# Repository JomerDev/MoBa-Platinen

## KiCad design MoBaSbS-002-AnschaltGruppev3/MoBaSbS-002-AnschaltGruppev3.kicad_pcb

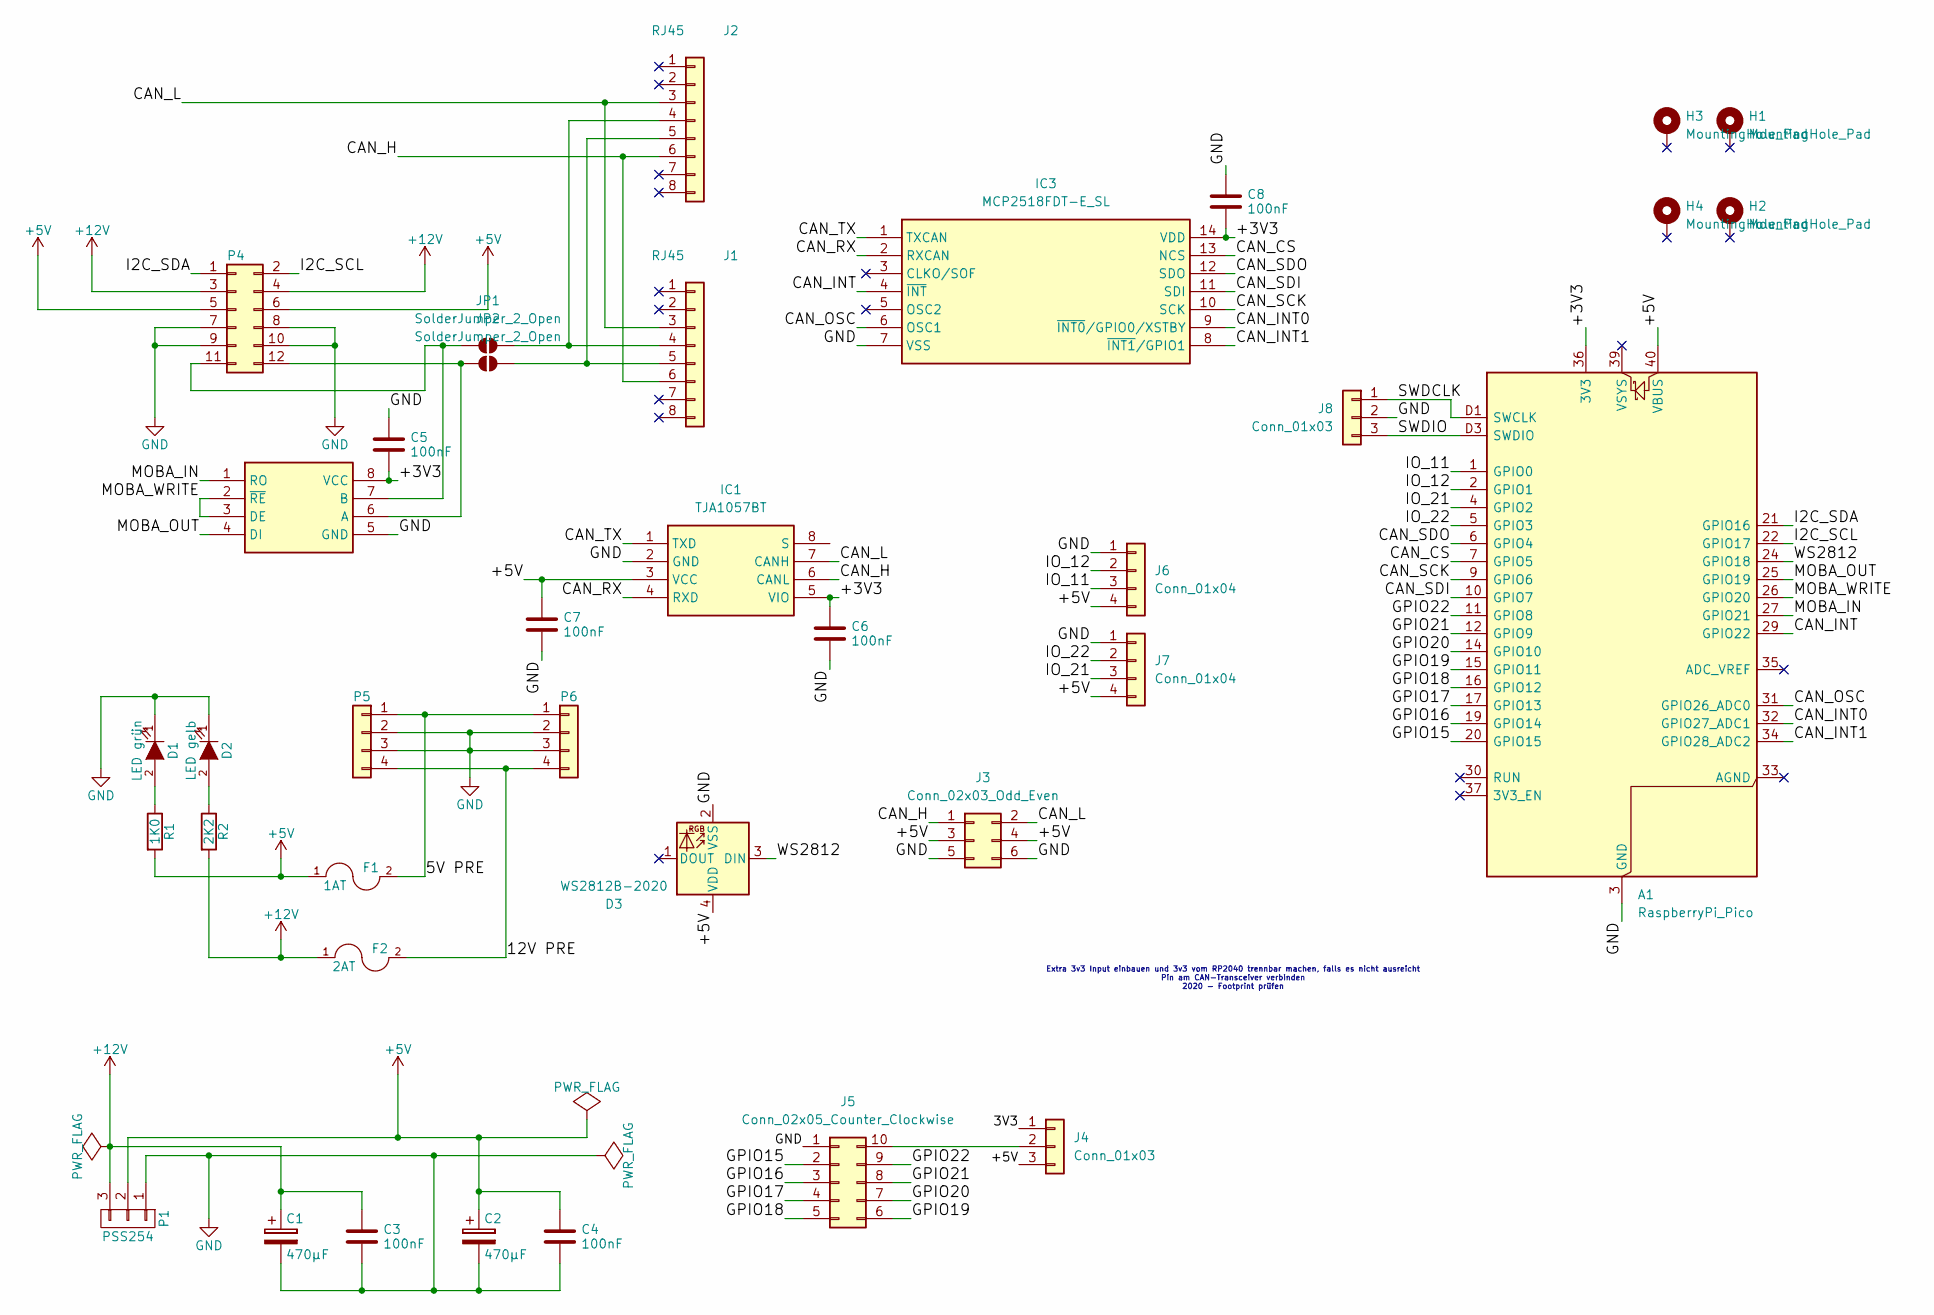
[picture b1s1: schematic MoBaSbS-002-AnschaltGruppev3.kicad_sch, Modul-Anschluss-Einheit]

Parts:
A1: RaspberryPi_Pico; RaspberryPi_Pico_Original_SMD_HandSolder
C1, C2: 470µF; CP_Radial_D8.0mm_P5.00mm
C3, C4: 100nF; C_1206_3216Metric
C5, C6, C7, C8: 100nF; C_0603_1608Metric
D1: LED grün; LED_1206_3216Metric
D2: LED gelb; LED_1206_3216Metric
D3: WS2812B-2020; LED_WS2812B-2020_PLCC4_2.0x2.0mm
F1: 1AT; Fuseholder_Littelfuse_Nano2_154x
F2: 2AT; Fuseholder_Littelfuse_Nano2_154x
H1, H2, H3, H4: MountingHole_Pad; MountingHole_2.7mm_M2.5_DIN965_Pad
IC1: TJA1057BT; SOIC127P600X175-8N; Manufacturer_Part_Number TJA1057BT
IC2: SP3485EN-L_TR; SOIC127P600X175-8N; Mouser Part Number 701-SP3485EN-L/TR
IC3: MCP2518FDT-E_SL; SOIC127P600X175-14N; Mouser Part Number 579-MCP2518FDT-E/SL
J1, J2: RJ45; RJ45_8
J3: Conn_02x03_Odd_Even; PinSocket_2x03_P2.54mm_Horizontal
J4, J8: Conn_01x03; PinHeader_1x03_P2.54mm_Vertical
J5: Conn_02x05_Counter_Clockwise; IDC-Header_2x05_P2.54mm_Vertical
J6, J7: Conn_01x04; Molex_KK-254_AE-6410-04A_1x04_P2.54mm_Vertical
JP1, JP2: SolderJumper_2_Open; SolderJumper-2_P1.3mm_Open_RoundedPad1.0x1.5mm
P1: PSS254; Molex_KK-254_AE-6410-03A_1x03_P2.54mm_Vertical
P4: 2x5_Buchse; PinSocket_2x06_P2.54mm_Horizontal
P5, P6: Wago; CONN_5566-04A_MOL
R1: 1K0; R_1206_3216Metric
R2: 2K2; R_1206_3216Metric

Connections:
+5V: A1.40 (VBUS), C2.1, C4.1, C7.1, D3.4 (VDD), F1.1, IC1.3 (VCC), J3.3, J3.4, J4.3, J6.4, J7.4, P1.2, P4.5, P4.6, R1.2
+12V: C1.1, C3.1, F2.1, P1.3, P4.3, P4.4, R2.2
/3V3: J4.1
/5V PRE: F1.2, P5.1, P6.1
/12V PRE: F2.2, P5.4, P6.4
/+3V3: A1.36 (3V3), C5.2, C6.1, C8.2, IC1.5 (VIO), IC2.8 (VCC), IC3.14 (VDD)
/CAN_CS: A1.7 (GPIO5), IC3.13 (NCS)
/CAN_H: IC1.6 (CANL), J1.6, J2.6, J3.1
/CAN_INT: A1.29 (GPIO22), IC3.4 (~INT)
/CAN_INT0: A1.32 (GPIO27_ADC1), IC3.9 (~INT0/GPIO0/XSTBY)
/CAN_INT1: A1.34 (GPIO28_ADC2), IC3.8 (~INT1/GPIO1)
/CAN_L: IC1.7 (CANH), J1.3, J2.3, J3.2
/CAN_OSC: A1.31 (GPIO26_ADC0), IC3.6 (OSC1)
/CAN_RX: IC1.4 (RXD), IC3.2 (RXCAN)
/CAN_SCK: A1.9 (GPIO6), IC3.10 (SCK)
/CAN_SDI: A1.10 (GPIO7), IC3.11 (SDI)
/CAN_SDO: A1.6 (GPIO4), IC3.12 (SDO)
/CAN_TX: IC1.1 (TXD), IC3.1 (TXCAN)
/GPIO15: A1.20 (GPIO15), J5.2
/GPIO16: A1.19 (GPIO14), J5.3
/GPIO17: A1.17 (GPIO13), J5.4
/GPIO18: A1.16 (GPIO12), J5.5
/GPIO19: A1.15 (GPIO11), J5.6
/GPIO20: A1.14 (GPIO10), J5.7
/GPIO21: A1.12 (GPIO9), J5.8
/GPIO22: A1.11 (GPIO8), J5.9
/I2C_SCL: A1.22 (GPIO17), P4.2
/I2C_SDA: A1.21 (GPIO16), P4.1
/IO_11: A1.1 (GPIO0), J6.3
/IO_12: A1.2 (GPIO1), J6.2
/IO_21: A1.4 (GPIO2), J7.3
/IO_22: A1.5 (GPIO3), J7.2
/MOBA_IN: A1.27 (GPIO21), IC2.1 (RO)
/MOBA_OUT: A1.25 (GPIO19), IC2.4 (DI)
/MOBA_WRITE: A1.26 (GPIO20), IC2.2 (~RE), IC2.3 (DE)
/SWDCLK: A1.D1 (SWCLK), J8.1
/SWDIO: A1.D3 (SWDIO), J8.3
/WS2812: A1.24 (GPIO18), D3.3 (DIN)
GND: A1.3 (GND), A1.8 (GND), A1.13 (GND), A1.18 (GND), A1.23 (GND), A1.28 (GND), A1.38 (GND), A1.D2 (GND), C1.2, C2.2, C3.2, C4.2, C5.1, C6.2, C7.2, C8.1, D1.1 (K), D2.1 (K), D3.2 (VSS), IC1.2 (GND), IC2.5 (GND), IC3.7 (VSS), J3.5, J3.6, J5.1, J6.1, J7.1, J8.2, P1.1, P4.7, P4.8, P4.9, P4.10, P5.2, P5.3, P6.2, P6.3
unnamed: D1.2 (A), R1.1
unnamed: D2.2 (A), R2.1
unnamed: IC2.6 (A), JP2.1 (A), P4.12
unnamed: IC2.7 (B), JP1.1 (A), P4.11
unnamed: J1.4, J2.4, JP1.2 (B)
unnamed: J1.5, J2.5, JP2.2 (B)
unnamed: J4.2, J5.10

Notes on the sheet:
Extra 3v3 Input einbauen und 3v3 vom RP2040 trennbar machen, falls es nicht ausreicht Pin am CAN-Transceiver verbinden 2020 - Footprint prüfen

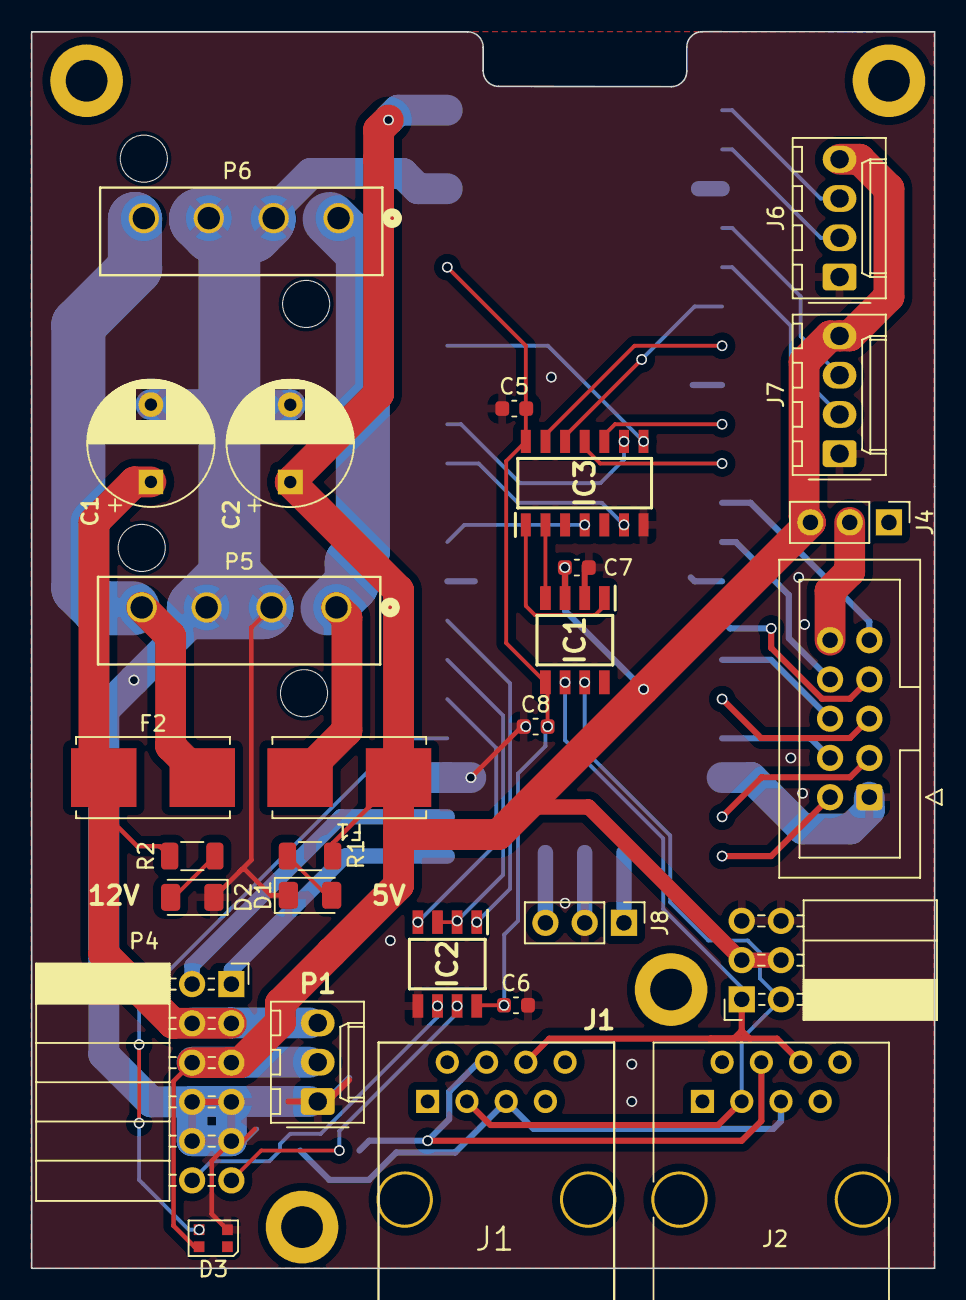
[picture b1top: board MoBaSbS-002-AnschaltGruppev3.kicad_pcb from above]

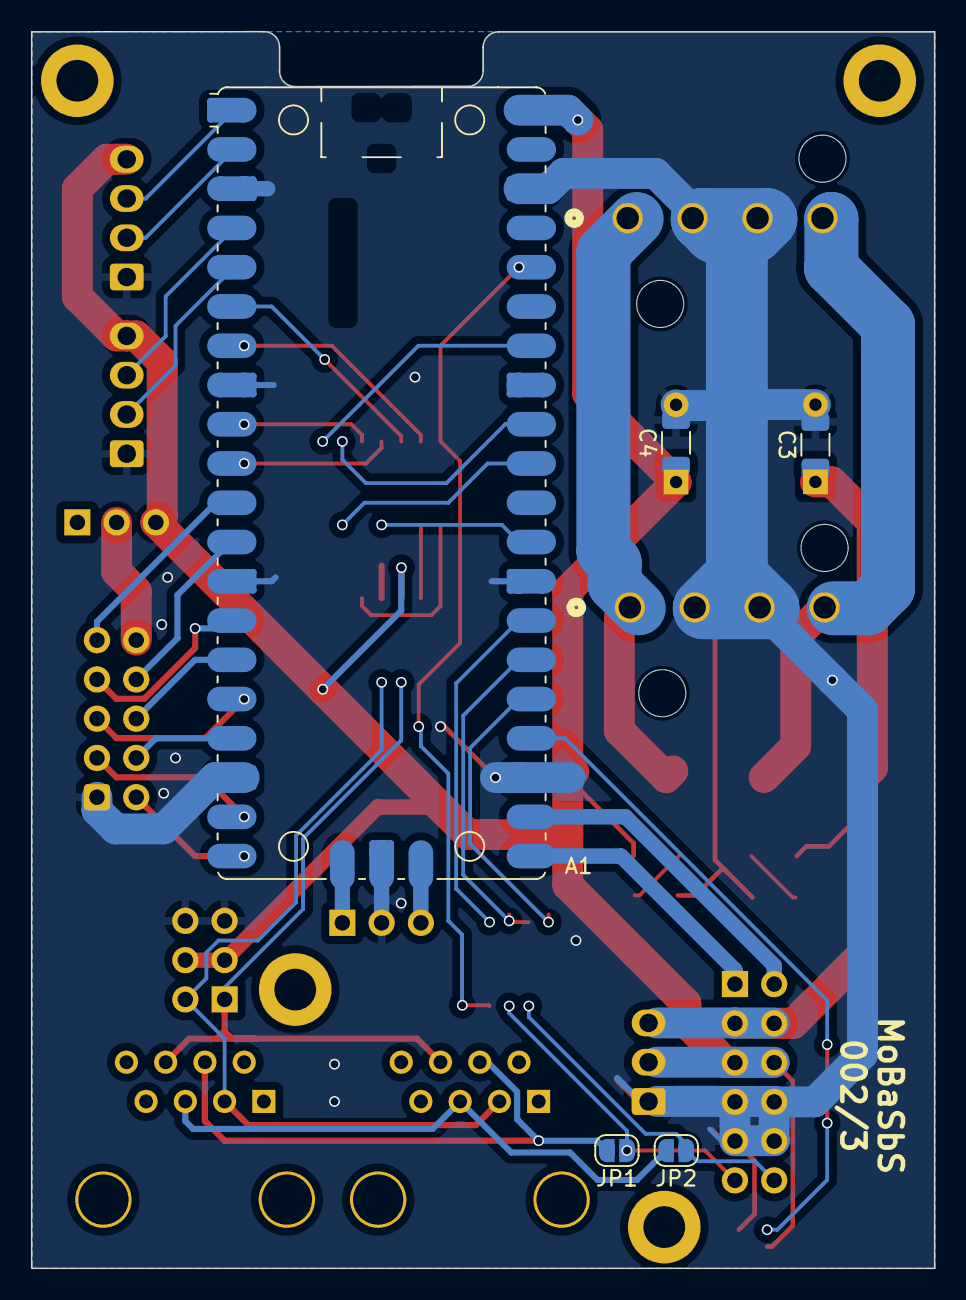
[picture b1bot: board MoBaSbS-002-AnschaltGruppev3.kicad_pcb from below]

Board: 2 copper layers, 58.4 x 80.0 mm, 37 parts (5 on the bottom side), 45 nets.

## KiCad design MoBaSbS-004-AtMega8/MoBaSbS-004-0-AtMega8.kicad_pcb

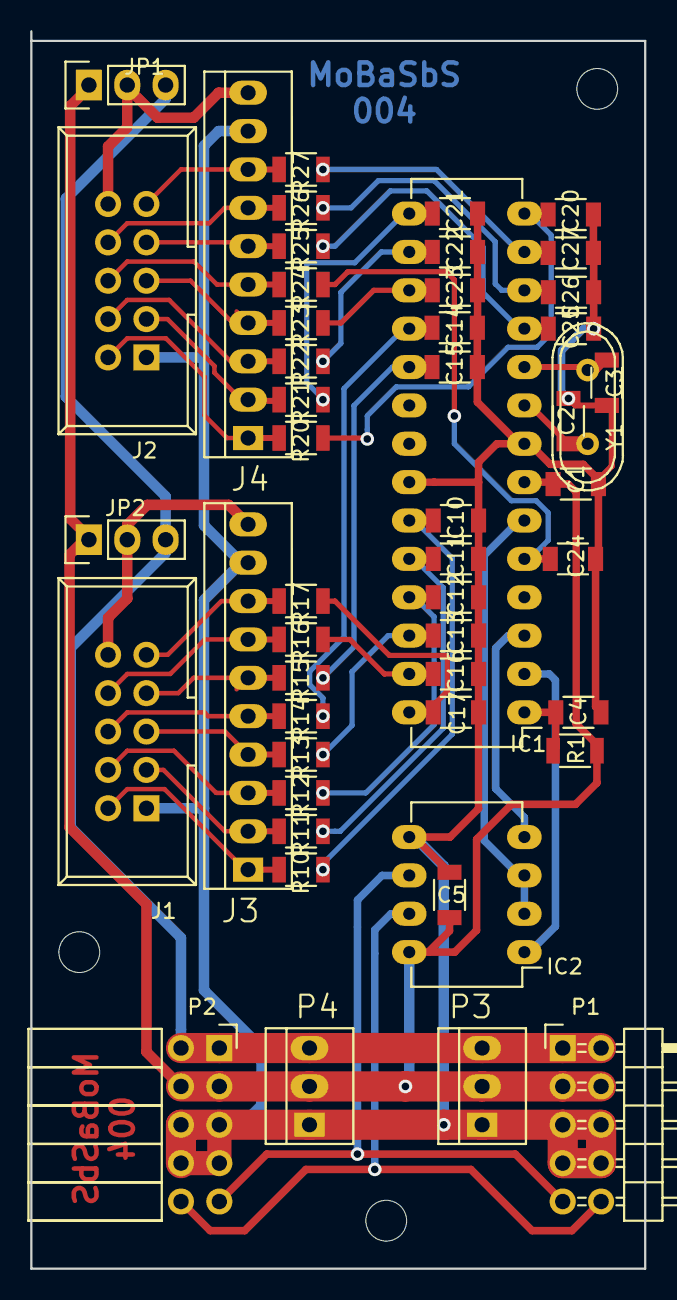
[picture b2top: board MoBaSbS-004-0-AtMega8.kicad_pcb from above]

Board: 2 copper layers, 40.6 x 81.9 mm, 51 parts (0 on the bottom side), 45 nets.

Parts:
C1, C4, C5: 100nF; C_1206
C2, C3: 33pF; C_1206
C10, C11, C12, C13, C14, C15, C16, C17, C20, C21, C22, C23, C24, C25, C26, C27: 47nF; C_1206
IC1: ATMEGA8A-P; DIP-28_W7.62mm_LongPads
IC2: MAX485; DIP-8_W7.62mm_LongPads
J1, J2: 10-Flachband; IDC_Header_Straight_10pins
J3, J4: PSS254-10P; PSS254-10G
JP1, JP2: JUMPER3; Pin_Header_Straight_1x03
P1: CONN_02X05; Pin_Header_Angled_2x05
P2: CONN_02X05; Socket_Strip_Angled_2x05
P3, P4: PSS-3G; PSS254-3G
R1: 10K0; R_1206
R10, R11, R12, R13, R14, R15, R16, R17, R20, R21, R22, R23, R24, R25, R26, R27: R; R_1206
Y1: 8MHz; Crystal_HC49-U_Vertical

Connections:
+5V: C1.1, C5.1, IC1.7, IC2.8, JP1.1, JP2.1, P1.3, P1.4, P2.3, P2.4, P3.2, P4.2, R1.1
+12V: JP1.3, JP2.3, P1.1, P1.2, P2.1, P2.2, P3.3, P4.3
GND: C1.2, C2.2, C3.2, C4.2, C5.2, C10.1, C11.1, C12.1, C13.1, C14.1, C15.1, C16.1, C17.1, C20.1, C21.1, C22.1, C23.1, C24.1, C25.1, C26.1, C27.1, IC1.8, IC1.22, IC2.5, J1.1, J2.1, J3.9, J4.9, P1.5, P1.6, P1.7, P1.8, P2.5, P2.6, P2.7, P2.8, P3.1, P4.1
unnamed: C2.1, IC1.9, Y1.1
unnamed: C3.1, IC1.10, Y1.2
unnamed: C4.1, IC1.1, R1.2
unnamed: C10.2, IC1.23, R10.2
unnamed: C11.2, IC1.24, R11.2
unnamed: C12.2, IC1.25, R12.2
unnamed: C13.2, IC1.26, R13.2
unnamed: C14.2, IC1.18, R14.2
unnamed: C15.2, IC1.19, R15.2
unnamed: C16.2, IC1.27, R16.2
unnamed: C17.2, IC1.28, R17.2
unnamed: C20.2, IC1.14, R20.2
unnamed: C21.2, IC1.15, R21.2
unnamed: C22.2, IC1.16, R22.2
unnamed: C23.2, IC1.17, R23.2
unnamed: C24.2, IC1.5, R24.2
unnamed: C25.2, IC1.11, R25.2
unnamed: C26.2, IC1.12, R26.2
unnamed: C27.2, IC1.13, R27.2
unnamed: IC1.2, IC2.1
unnamed: IC1.3, IC2.4
unnamed: IC1.6, IC2.2, IC2.3
unnamed: IC2.6, P1.9, P2.9
unnamed: IC2.7, P1.10, P2.10
unnamed: J1.2, J3.1, R10.1
unnamed: J1.3, J3.2, R11.1
unnamed: J1.4, J3.3, R12.1
unnamed: J1.5, J3.4, R13.1
unnamed: J1.6, J3.5, R14.1
unnamed: J1.7, J3.6, R15.1
unnamed: J1.8, J3.7, R16.1
unnamed: J1.9, J3.8, R17.1
unnamed: J1.10, J3.10, JP2.2
unnamed: J2.2, J4.1, R20.1
unnamed: J2.3, J4.2, R21.1
unnamed: J2.4, J4.3, R22.1
unnamed: J2.5, J4.4, R23.1
unnamed: J2.6, J4.5, R24.1
unnamed: J2.7, J4.6, R25.1
unnamed: J2.8, J4.7, R26.1
unnamed: J2.9, J4.8, R27.1
unnamed: J2.10, J4.10, JP1.2

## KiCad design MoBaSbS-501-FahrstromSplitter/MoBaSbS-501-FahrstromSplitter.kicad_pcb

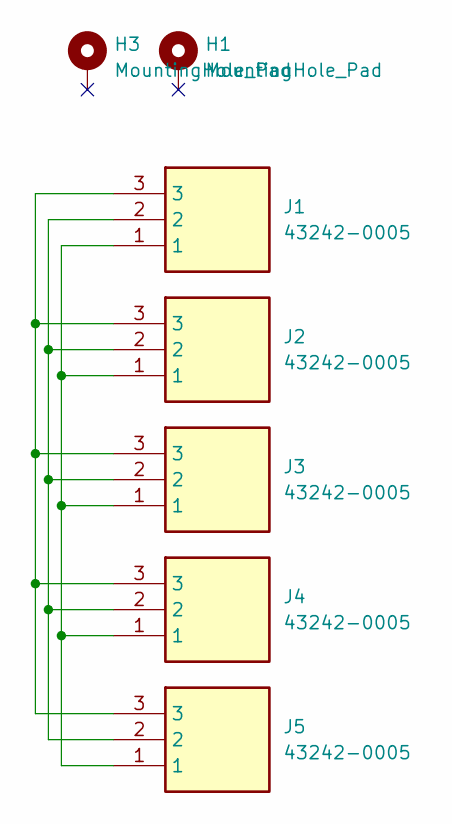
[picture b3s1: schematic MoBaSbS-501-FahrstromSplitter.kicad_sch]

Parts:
H1, H3: MountingHole_Pad; MountingHole_2.7mm_M2.5_DIN965_Pad
J1, J2, J3, J4, J5: 43242-0005; Molex_MiniFitJr_1x3_PCB; Mouser Part Number 538-43242-0005

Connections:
unnamed: J1.1, J2.1, J3.1, J4.1, J5.1
unnamed: J1.2, J2.2, J3.2, J4.2, J5.2
unnamed: J1.3, J2.3, J3.3, J4.3, J5.3

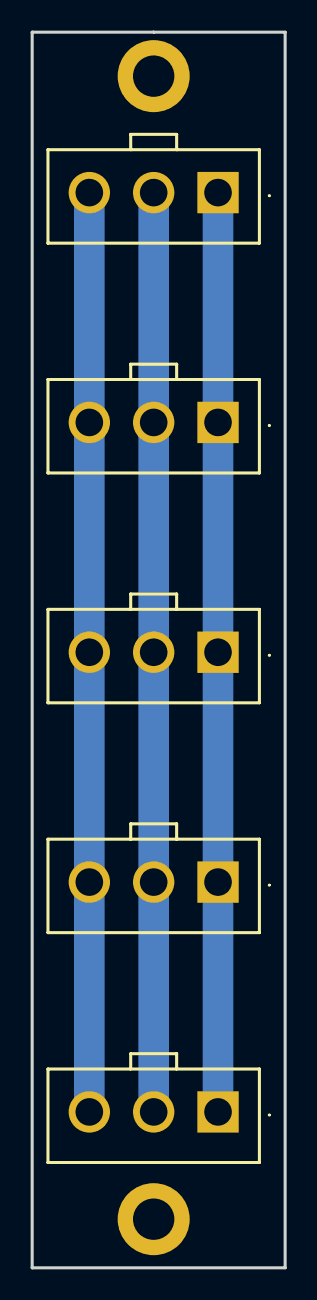
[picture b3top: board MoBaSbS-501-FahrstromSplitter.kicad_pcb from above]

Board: 2 copper layers, 16.5 x 80.6 mm, 7 parts (0 on the bottom side), 3 nets.
